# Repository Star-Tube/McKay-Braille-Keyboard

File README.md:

# McKay-Braille-Keyboard
A repository for containing all information regarding a design for a braille keyboard intended for public distribution.

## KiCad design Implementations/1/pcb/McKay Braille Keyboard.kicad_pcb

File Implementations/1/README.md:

# Implementation 1

This is my first attempt to implement this design.  
It uses a two layer PCB designed in Kicad, 14 cherry MX switches, 14 DO-35 diodes and an Arduino Pro Micro as well as (soon) a printed case and front as well as keycaps of choice.

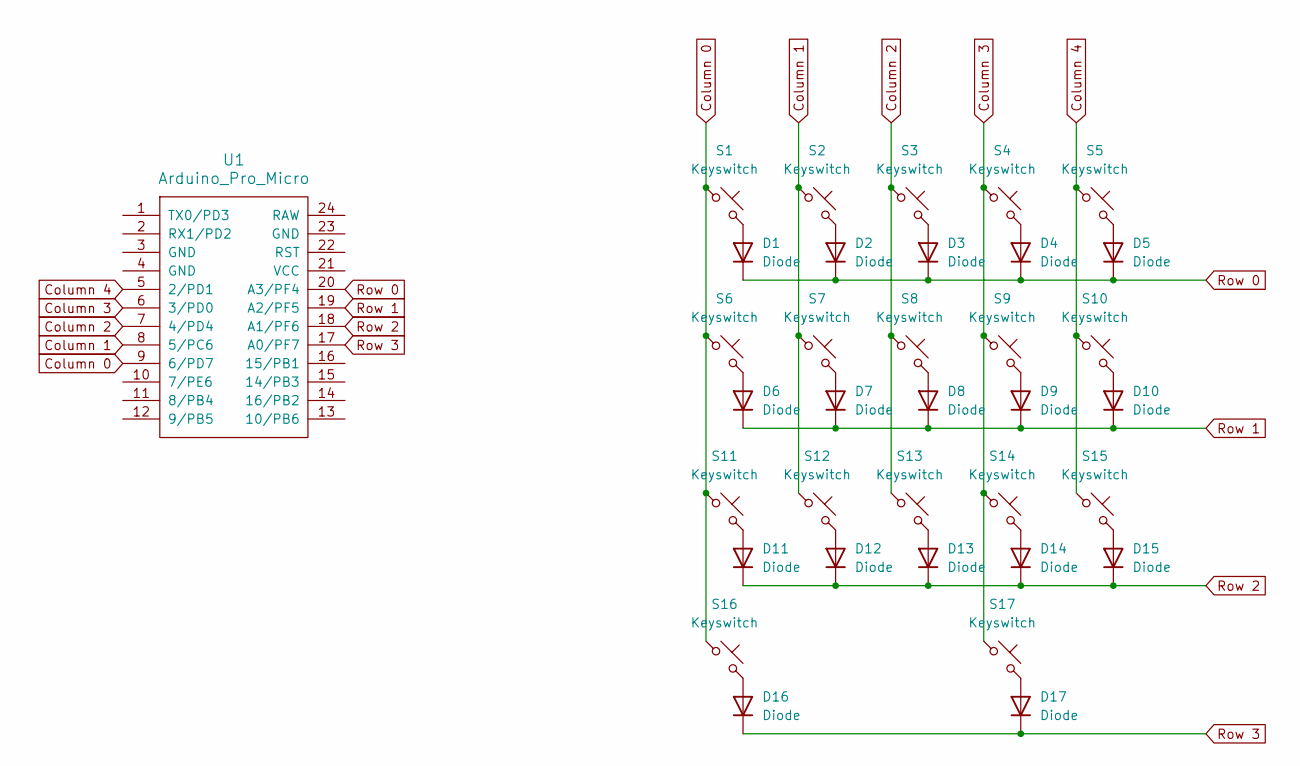
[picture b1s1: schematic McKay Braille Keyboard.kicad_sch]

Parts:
D1, D2, D3, D4, D5, D6, D7, D8, D9, D10, D11, D12, D13, D14, D15, D16, D17: Diode; Diode_DO-35
S1, S2, S3, S4, S5, S6, S7, S8, S9, S10, S11, S12, S13, S14, S15, S16, S17: Keyswitch; MX_PCB_1.00u
U1: Arduino_Pro_Micro

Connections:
Column 0: S1.1, S6.1, S11.1, S16.1, U1.9 (6/PD7)
Column 1: S2.1, S7.1, S12.1, U1.8 (5/PC6)
Column 2: S3.1, S8.1, S13.1, U1.7 (4/PD4)
Column 3: S4.1, S9.1, S14.1, S17.1, U1.6 (3/PD0)
Column 4: S5.1, S10.1, S15.1, U1.5 (2/PD1)
unnamed: D1.2 (A), S1.2
unnamed: D2.2 (A), S2.2
unnamed: D3.2 (A), S3.2
unnamed: D4.2 (A), S4.2
unnamed: D5.2 (A), S5.2
unnamed: D6.2 (A), S6.2
unnamed: D7.2 (A), S7.2
unnamed: D8.2 (A), S8.2
unnamed: D9.2 (A), S9.2
unnamed: D10.2 (A), S10.2
unnamed: D11.2 (A), S11.2
unnamed: D12.2 (A), S12.2
unnamed: D13.2 (A), S13.2
unnamed: D14.2 (A), S14.2
unnamed: D15.2 (A), S15.2
unnamed: D16.2 (A), S16.2
unnamed: D17.2 (A), S17.2
Row 0: D1.1 (K), D2.1 (K), D3.1 (K), D4.1 (K), D5.1 (K), U1.20 (A3/PF4)
Row 1: D6.1 (K), D7.1 (K), D8.1 (K), D9.1 (K), D10.1 (K), U1.19 (A2/PF5)
Row 2: D11.1 (K), D12.1 (K), D13.1 (K), D14.1 (K), D15.1 (K), U1.18 (A1/PF6)
Row 3: D16.1 (K), D17.1 (K), U1.17 (A0/PF7)

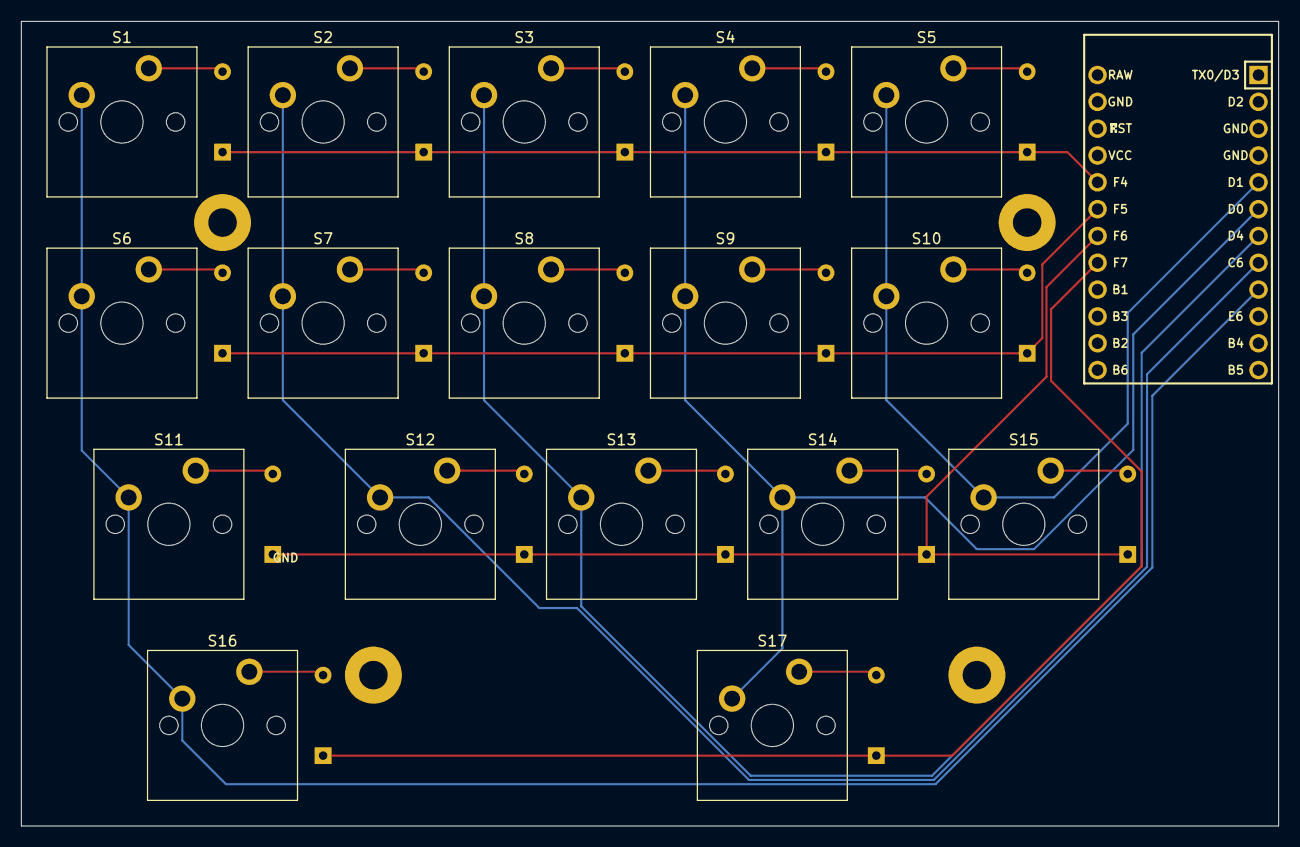
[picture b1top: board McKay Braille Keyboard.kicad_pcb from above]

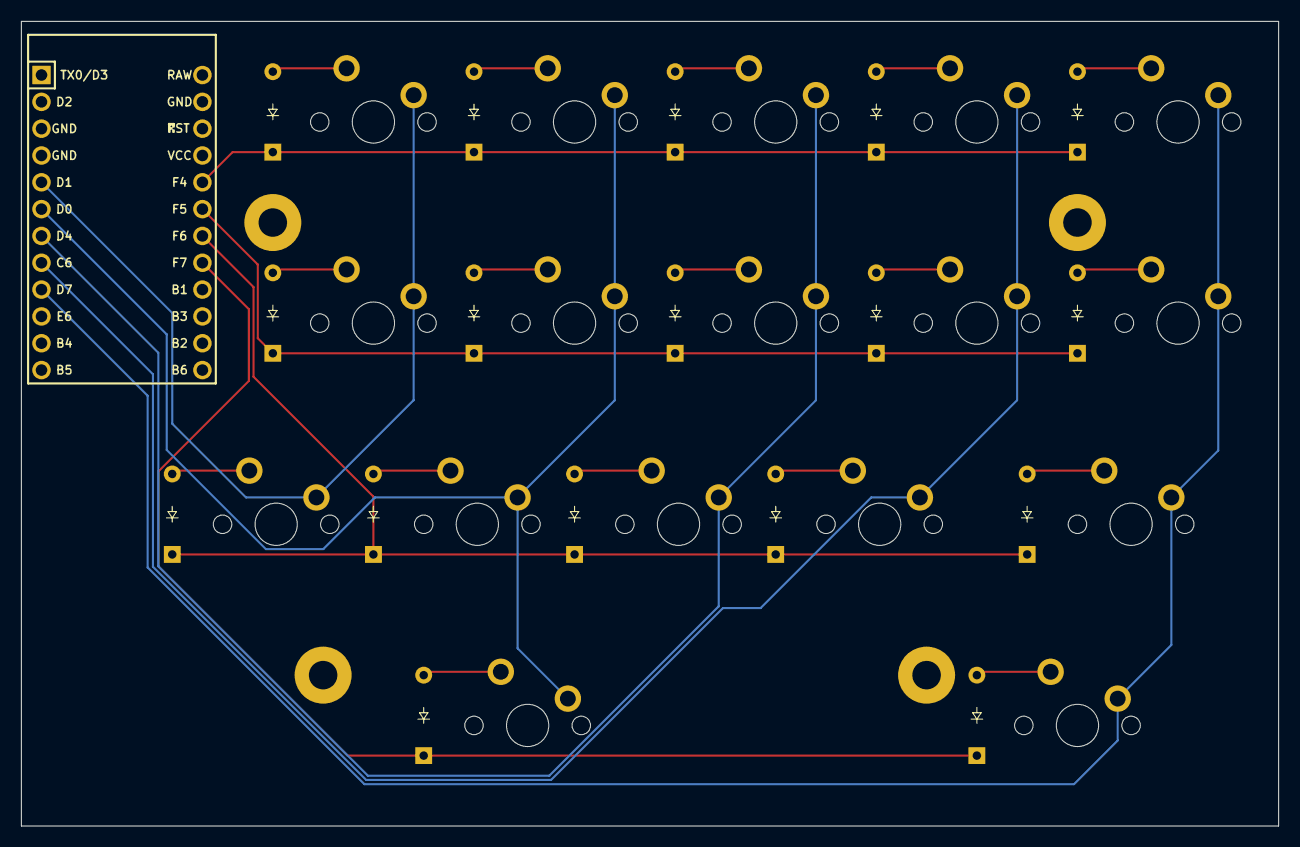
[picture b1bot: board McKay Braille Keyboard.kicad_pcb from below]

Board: 2 copper layers, 119.1 x 76.2 mm, 35 parts (18 on the bottom side), 26 nets.

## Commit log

2025-09-04 Create Specification.md
    Create a specifications file which contains a description of the design.
2025-09-04 Add Figure 1.png via upload
    Add Figure 1.png for use with Specification.md
2025-09-04 Create a folder to upload an implementation information into
2025-09-04 Update Specification.md
    Update Specification.md to reference the new Figure 2.png file
2025-09-04 Create README.md
    Basic readme.md to explain the implementation and what it (will) include.
2025-09-04 Rename Implementations/1/McKay Braille Keyboard.kicad_sch to Implementations/1/pcb/McKay Braille Keyboard.kicad_sch
2025-09-04 Rename Implementations/1/McKay Braille Keyboard.kicad_pcb to Implementations/1/pcb/McKay Braille Keyboard.kicad_pcb
2025-09-04 Rename Implementations/1/McKay Braille Keyboard.kicad_prl to Implementations/1/pcb/McKay Braille Keyboard.kicad_prl
2025-09-04 Rename Implementations/1/McKay Braille Keyboard.kicad_pro to Implementations/1/pcb/McKay Braille Keyboard.kicad_pro
2025-09-04 Rename Implementations/1/fabrication-toolkit-options.json to Implementations/1/pcb/fabrication-toolkit-options.json
2025-09-04 Rename Implementations/1/fp-info-cache to Implementations/1/pcb/fp-info-cache
2025-09-04 Rename Implementations/1/Case.blend to Implementations/1/Case/Case.blend
2025-09-04 Rename Implementations/1/Case.fbx to Implementations/1/Case/Case.fbx
